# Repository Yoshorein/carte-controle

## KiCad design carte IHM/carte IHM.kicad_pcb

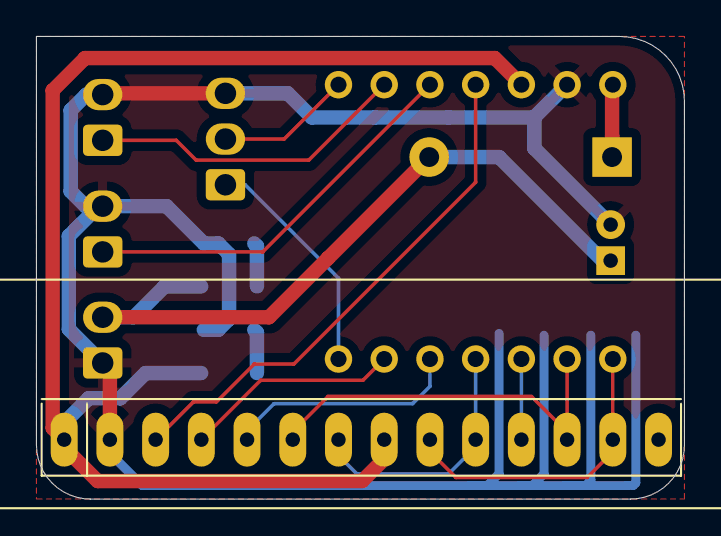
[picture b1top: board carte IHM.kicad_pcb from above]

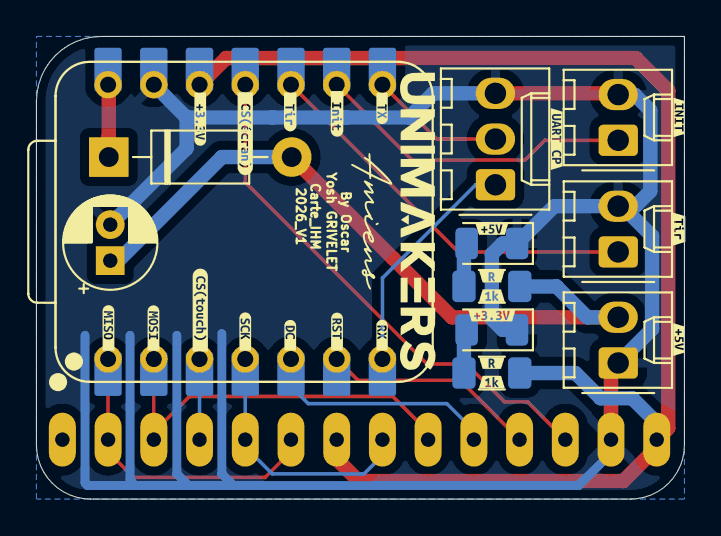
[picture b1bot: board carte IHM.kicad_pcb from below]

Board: 2 copper layers, 36.0 x 25.7 mm, 34 parts (33 on the bottom side), 17 nets.

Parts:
C5: 100µF; CP_Radial_D5.0mm_P2.00mm
D1: D_Shottky; D_DO-41_SOD81_P10.16mm_Horizontal
D2, D3: LED_Small; LED_1206_3216Metric
J1: tirette; Molex_KK-254_AE-6410-02A_1x02_P2.54mm_Vertical
J2: UART CP; Molex_KK-254_AE-6410-03A_1x03_P2.54mm_Vertical
J3: init; Molex_KK-254_AE-6410-02A_1x02_P2.54mm_Vertical
J4: Conn_01x02; Molex_KK-254_AE-6410-02A_1x02_P2.54mm_Vertical
R3, R5: 1k; R_1206_3216Metric_Pad1.30x1.75mm_HandSolder
U1: XIAO-ESP32-S3-DIP; XIAO-ESP32S3-DIP
U2: TFT_320x240; TFT-320x240
kibuzzard-690E93A6: G***; kibuzzard-690E93A6
kibuzzard-690E93B3: G***; kibuzzard-690E93B3
kibuzzard-690E924D: G***; kibuzzard-690E924D
kibuzzard-690E943A, kibuzzard-690E943A#2: G***; kibuzzard-690E943A
kibuzzard-690E9271: G***; kibuzzard-690E9271
kibuzzard-690E9406, kibuzzard-690E9406#2: G***; kibuzzard-690E9406
kibuzzard-691080A1: G***; kibuzzard-691080A1
kibuzzard-691080B6: G***; kibuzzard-691080B6
kibuzzard-691080CB: G***; kibuzzard-691080CB
kibuzzard-691080DD: G***; kibuzzard-691080DD
kibuzzard-691080F8: G***; kibuzzard-691080F8
kibuzzard-691084CF: G***; kibuzzard-691084CF
kibuzzard-691084E9: G***; kibuzzard-691084E9
kibuzzard-6910807D: G***; kibuzzard-6910807D
kibuzzard-6910808E: G***; kibuzzard-6910808E
kibuzzard-69108106: G***; kibuzzard-69108106
kibuzzard-69108124: G***; kibuzzard-69108124
kibuzzard-69108131: G***; kibuzzard-69108131
kibuzzard-69108151: G***; kibuzzard-69108151
kibuzzard-69108163: G***; kibuzzard-69108163

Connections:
+3.3V: R3.1, U1.12 (VCC_3V3), U2.1 (VCC), U2.8 (LED)
+5V: C5.1, D1.2 (A), J4.2, R5.1
CS (touch): U1.3 (GPIO3/D2/A2), U2.11
CS (écran): U1.11 (GPIO9/D10/A10/MOSI), U2.3 (CS)
DC: U1.5 (GPIO5/D4/I2C_SDA), U2.5 (DC)
GND: C5.2, D2.1 (K), D3.1 (K), J1.2, J2.3, J3.2, J4.1, U1.13 (GND), U2.2 (GND)
MISO: U1.1 (GPIO1/D0/A0), U2.9 (MISO), U2.13
MOSI: U1.2 (GPIO2/DA/A1), U2.6 (MOSI), U2.12
unnamed: D1.1 (K), U1.14 (VBUS)
unnamed: D2.2 (A), R5.2
unnamed: D3.2 (A), R3.2
RST: U1.6 (GPIO9/D5/I2C_SCL), U2.4 (RST)
RX: J2.1, U1.7 (U0TXD/D6/TX)
SCK: U1.4 (GPIO4/D3/A3), U2.7 (SCK), U2.10
TIRETTE: J1.1, U1.10 (GPIO8/D9/A9/MISO)
TX: J2.2, U1.8 (U0RXD/D7/RX)
init: J3.1, U1.9 (GPIO7/D8/A8/SCK)

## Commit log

2025-11-09 V1.1 avec étiquetage
2025-11-09 fixes
2025-11-09 ptitoublie
2025-11-12 pas grand chose
